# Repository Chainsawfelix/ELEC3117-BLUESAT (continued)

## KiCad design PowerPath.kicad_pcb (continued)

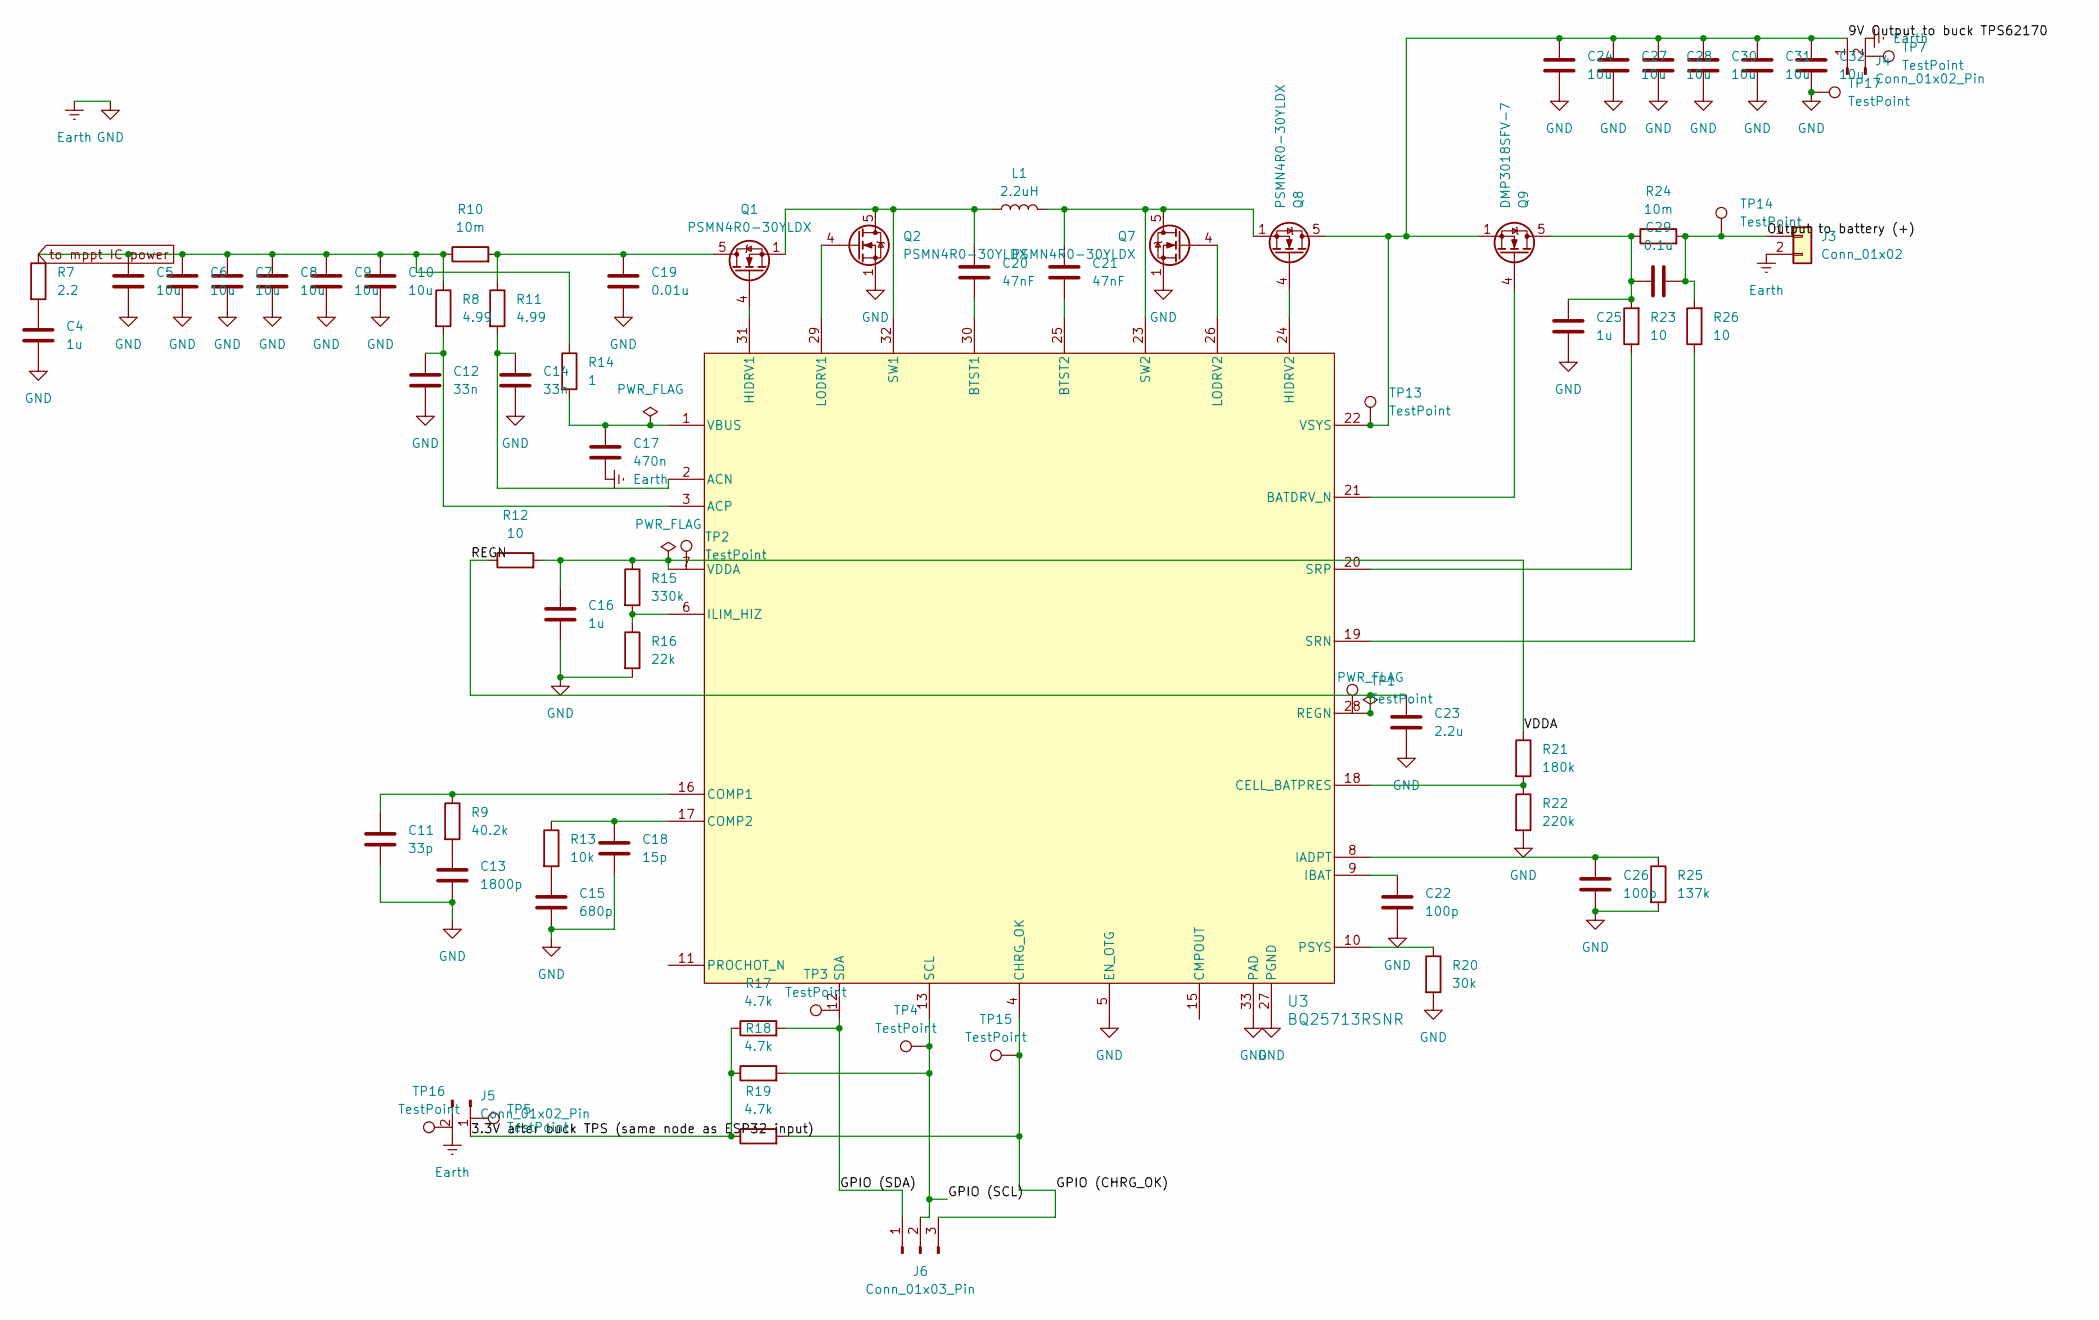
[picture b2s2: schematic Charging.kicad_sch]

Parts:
C4, C16, C25: 1u; C_0805_2012Metric_Pad1.18x1.45mm_HandSolder
C5, C6, C7, C8, C9, C10, C24, C27, C28, C30, C31, C32: 10u; C_1206_3216Metric_Pad1.33x1.80mm_HandSolder
C11: 33p; C_0603_1608Metric_Pad1.08x0.95mm_HandSolder
C12, C14: 33n; C_0805_2012Metric_Pad1.18x1.45mm_HandSolder
C13: 1800p; C_0603_1608Metric_Pad1.08x0.95mm_HandSolder
C15: 680p; C_0603_1608Metric_Pad1.08x0.95mm_HandSolder
C17: 470n; C_1206_3216Metric_Pad1.33x1.80mm_HandSolder
C18: 15p; C_0603_1608Metric_Pad1.08x0.95mm_HandSolder
C19: 0.01u; C_0603_1608Metric_Pad1.08x0.95mm_HandSolder
C20, C21: 47nF; C_0603_1608Metric_Pad1.08x0.95mm_HandSolder
C22, C26: 100p; C_0603_1608Metric_Pad1.08x0.95mm_HandSolder
C23: 2.2u; C_0805_2012Metric_Pad1.18x1.45mm_HandSolder
C29: 0.1u; C_0603_1608Metric_Pad1.08x0.95mm_HandSolder
J3: Conn_01x02; XT60_Pigtail_14AWG
J4, J5: Conn_01x02_Pin; JST_XH_B2B-XH-A_1x02_P2.50mm_Vertical
J6: Conn_01x03_Pin; JST_XH_B3B-XH-A_1x03_P2.50mm_Vertical
L1: 2.2uH; L_Bourns_SRP1050WA
Q1, Q2, Q7, Q8: PSMN4R0-30YLDX; LFPAK56
Q9: DMP3018SFV-7; Diodes_PowerDI3333-8
R7: 2.2; R_0603_1608Metric_Pad0.98x0.95mm_HandSolder
R8, R11: 4.99; R_0603_1608Metric_Pad0.98x0.95mm_HandSolder
R9: 40.2k; R_0805_2012Metric_Pad1.20x1.40mm_HandSolder
R10, R24: 10m; R_0805_2012Metric_Pad1.20x1.40mm_HandSolder
R12: 10; R_0805_2012Metric_Pad1.20x1.40mm_HandSolder
R13: 10k; R_0603_1608Metric_Pad0.98x0.95mm_HandSolder
R14: 1; R_0805_2012Metric_Pad1.20x1.40mm_HandSolder
R15: 330k; R_0805_2012Metric_Pad1.20x1.40mm_HandSolder
R16: 22k; R_0805_2012Metric_Pad1.20x1.40mm_HandSolder
R17, R18, R19: 4.7k; R_0805_2012Metric_Pad1.20x1.40mm_HandSolder
R20: 30k; R_0805_2012Metric_Pad1.20x1.40mm_HandSolder
R21: 180k; R_0805_2012Metric_Pad1.20x1.40mm_HandSolder
R22: 220k; R_0805_2012Metric_Pad1.20x1.40mm_HandSolder
R23, R26: 10; R_0603_1608Metric_Pad0.98x0.95mm_HandSolder
R25: 137k; R_0805_2012Metric_Pad1.20x1.40mm_HandSolder
TP1, TP2, TP3, TP4, TP5, TP13, TP14, TP15: TestPoint; TestPoint_Pad_D1.0mm
TP7, TP16, TP17: TestPoint; TestPoint_Loop_D2.50mm_Drill1.0mm
U3: BQ25713RSNR; QFN-32-1EP_4x4mm_P0.4mm_EP2.65x2.65mm_ThermalVias

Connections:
/MPPT_circuit/3.3V after buck TPS (same node as ESP32 input): J5.1, R17.1, R18.1, R19.1, TP5.1 (1_1)
/MPPT_circuit/9V Output to buck TPS62170: C24.1, C27.1, C28.1, C30.1, C31.1, C32.1, J4.1, Q8.5 (D), Q9.1 (S), Q9.2 (S), Q9.3 (S), TP13.1 (1_1), U3.22 (VSYS)
/MPPT_circuit/GPIO (CHRG_OK): J6.3, R19.2, TP15.1 (1_1), U3.4 (CHRG_OK)
/MPPT_circuit/GPIO (SCL): J6.2, R18.2, TP4.1 (1_1), U3.13 (SCL)
/MPPT_circuit/GPIO (SDA): J6.1, R17.2, TP3.1 (1_1), U3.12 (SDA)
/MPPT_circuit/Output to battery (+): C29.2, J3.1, R24.2, R26.2, TP14.1 (1_1)
/MPPT_circuit/REGN: C23.1, R12.1, TP1.1 (1_1), U3.28 (REGN)
/MPPT_circuit/VDDA: C16.1, R12.2, R15.1, R21.1, TP2.1 (1_1), U3.7 (VDDA)
Earth: C4.2, C5.2, C6.2, C7.2, C8.2, C9.2, C10.2, C11.2, C12.2, C13.2, C14.2, C15.2, C16.2, C17.2, C18.2, C19.2, C22.2, C23.2, C24.2, C25.2, C26.2, C27.2, C28.2, C30.2, C31.2, C32.2, J3.2, J4.2, J5.2, Q2.1 (S), Q2.2 (S), Q2.3 (S), Q7.1 (S), Q7.2 (S), Q7.3 (S), R16.2, R20.2, R22.2, R25.2, TP7.1 (1_1), TP16.1 (1_1), TP17.1 (1_1), U3.5 (EN_OTG), U3.27 (PGND), U3.33 (PAD); also elsewhere on the board
unnamed: C4.1, R7.2
unnamed: C13.1, R9.2
unnamed: C15.1, R13.2
unnamed: C19.1, Q1.5 (D), R10.2, R11.1
unnamed: Q1.4 (G), U3.31 (HIDRV1)
unnamed: C20.1, L1.1, Q1.1 (S), Q1.2 (S), Q1.3 (S), Q2.5 (D), U3.32 (SW1)
unnamed: Q2.4 (G), U3.29 (LODRV1)
unnamed: C21.1, L1.2, Q7.5 (D), Q8.1 (S), Q8.2 (S), Q8.3 (S), U3.23 (SW2)
unnamed: Q7.4 (G), U3.26 (LODRV2)
unnamed: Q8.4 (G), U3.24 (HIDRV2)
unnamed: C25.1, C29.1, Q9.5 (D), R23.2, R24.1
unnamed: Q9.4 (G), U3.21 (BATDRV_N)
unnamed: C14.1, R11.2, U3.2 (ACN)
unnamed: C12.1, R8.2, U3.3 (ACP)
unnamed: C20.2, U3.30 (BTST1)
unnamed: C21.2, U3.25 (BTST2)
unnamed: R21.2, R22.1, U3.18 (CELL_BATPRES)
unnamed: C11.1, R9.1, U3.16 (COMP1)
unnamed: C18.1, R13.1, U3.17 (COMP2)
unnamed: C26.1, R25.1, U3.8 (IADPT)
unnamed: C22.1, U3.9 (IBAT)
unnamed: R15.2, R16.1, U3.6 (ILIM_HIZ)
unnamed: R20.1, U3.10 (PSYS)
unnamed: R26.1, U3.19 (SRN)
unnamed: R23.1, U3.20 (SRP)
unnamed: C17.1, R14.2, U3.1 (VBUS)
to mppt IC power: C5.1, C6.1, C7.1, C8.1, C9.1, C10.1, R7.1, R8.1, R10.1, R14.1; also elsewhere on the board

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
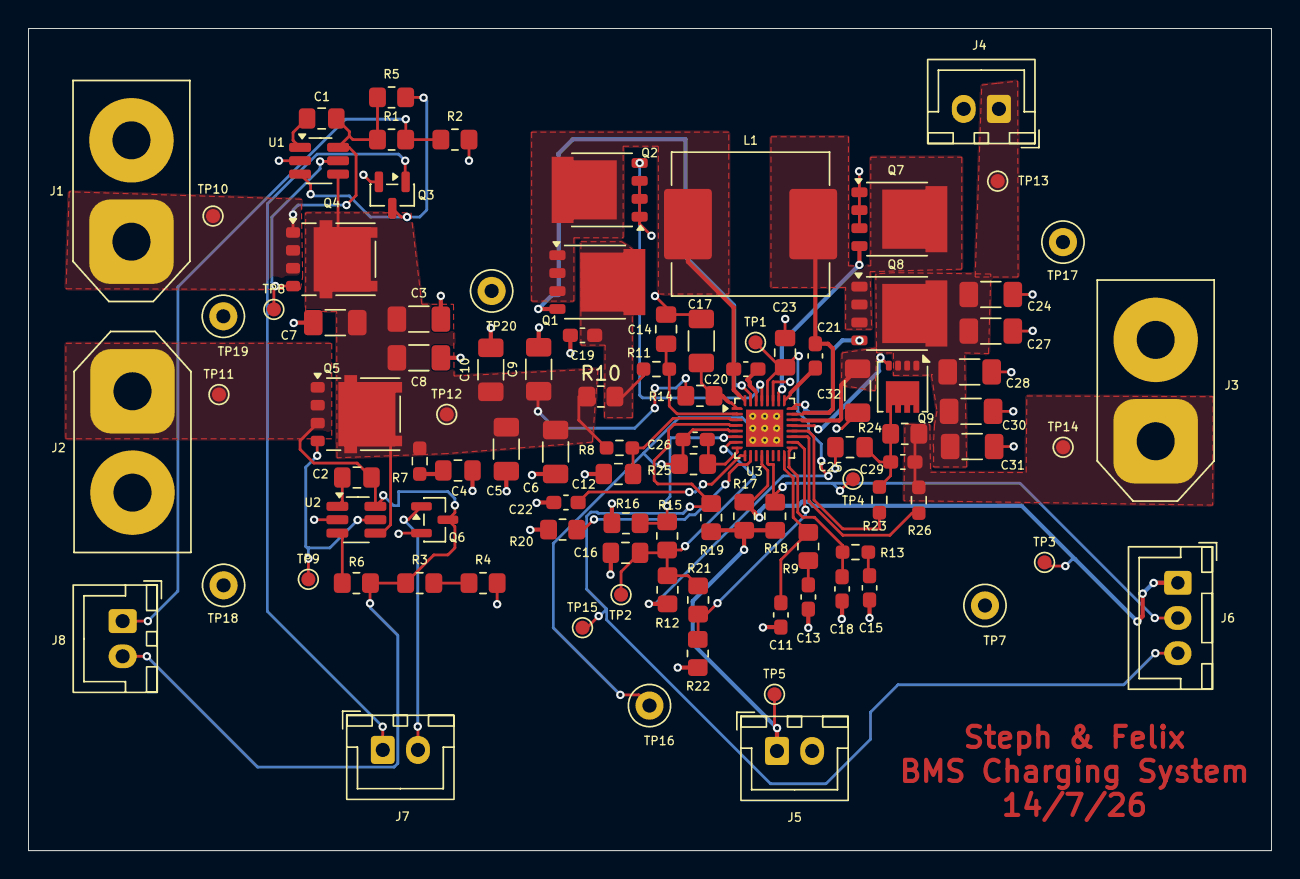
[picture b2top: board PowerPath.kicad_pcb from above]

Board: 2 copper layers, 88.3 x 58.4 mm, 98 parts (0 on the bottom side), 48 nets.

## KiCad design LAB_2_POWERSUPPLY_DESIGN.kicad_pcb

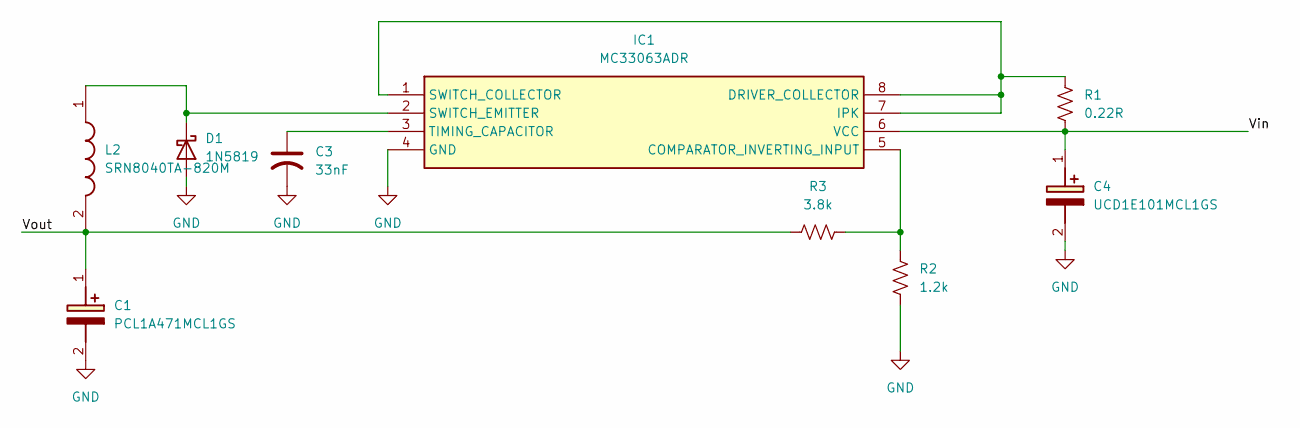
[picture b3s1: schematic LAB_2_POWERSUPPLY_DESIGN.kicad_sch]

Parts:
C1: PCL1A471MCL1GS; CAPAE830X1040N; Mouser Part Number 647-PCL1A471MCL1GS
C3: 33nF; C_0805_2012Metric_Pad1.18x1.45mm_HandSolder
C4: UCD1E101MCL1GS; CAPAE660X800N; Mouser Part Number 647-UCD1E101MCL1GS
D1: 1N5819; D_SMA_Handsoldering
IC1: MC33063ADR; SOIC127P600X175-8N; Mouser Part Number 595-MC33063ADR
L2: SRN8040TA-820M; INDPM8080X400N; Mouser Part Number 652-SRN8040TA-820M
R1: 0.22R; R_0805_2012Metric_Pad1.20x1.40mm_HandSolder
R2: 1.2k; R_0805_2012Metric_Pad1.20x1.40mm_HandSolder
R3: 3.8k; R_0805_2012Metric_Pad1.20x1.40mm_HandSolder

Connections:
/Vin: C4.1 (+), IC1.6 (VCC), R1.2
/Vout: C1.1 (+), L2.2, R3.2
GND: C1.2 (-), C3.2, C4.2 (-), D1.2 (A), IC1.4 (GND), R2.1
unnamed: D1.1 (K), IC1.2 (SWITCH_EMITTER), L2.1
unnamed: IC1.5 (COMPARATOR_INVERTING_INPUT), R2.2, R3.1
unnamed: IC1.1 (SWITCH_COLLECTOR), IC1.7 (IPK), IC1.8 (DRIVER_COLLECTOR), R1.1
unnamed: C3.1, IC1.3 (TIMING_CAPACITOR)

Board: 2 copper layers, 9 parts (0 on the bottom side), 7 nets, no tracks yet.

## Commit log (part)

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2026-06-27 Add files via upload
    LAB2 PSU design files for Kicad for future PCB design reference
2026-06-27 Add files via upload
    Stephanie's Draw.io block diagram draft 22/06/2022 on Discord
2026-06-27 Revert "Add files via upload"
2026-06-27 Removal of accidental PSU schem files from block diagram branch
2026-06-27 Remove file from main (accidental merge)
2026-06-27 Added Felix_DRAFT_BMS_ELEC3117.drawio
2026-06-30 Add files via upload
    Added esp32-s3 schematic and also BQ76952
